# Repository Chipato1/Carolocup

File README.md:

# Carolocup
Zentrales Repository für die Carolo-Cup Software

Driving Vision Compile command: 
g++ $(pkg-config --cflags --libs /usr/local/Cellar/opencv/4.1.1_2/lib/pkgconfig/opencv4.pc) -std=c++11 /Users/beni/Desktop/Studium/Studienarbeit/OpenCV/QRCode/QRCode/main.cpp -o TestProgramm

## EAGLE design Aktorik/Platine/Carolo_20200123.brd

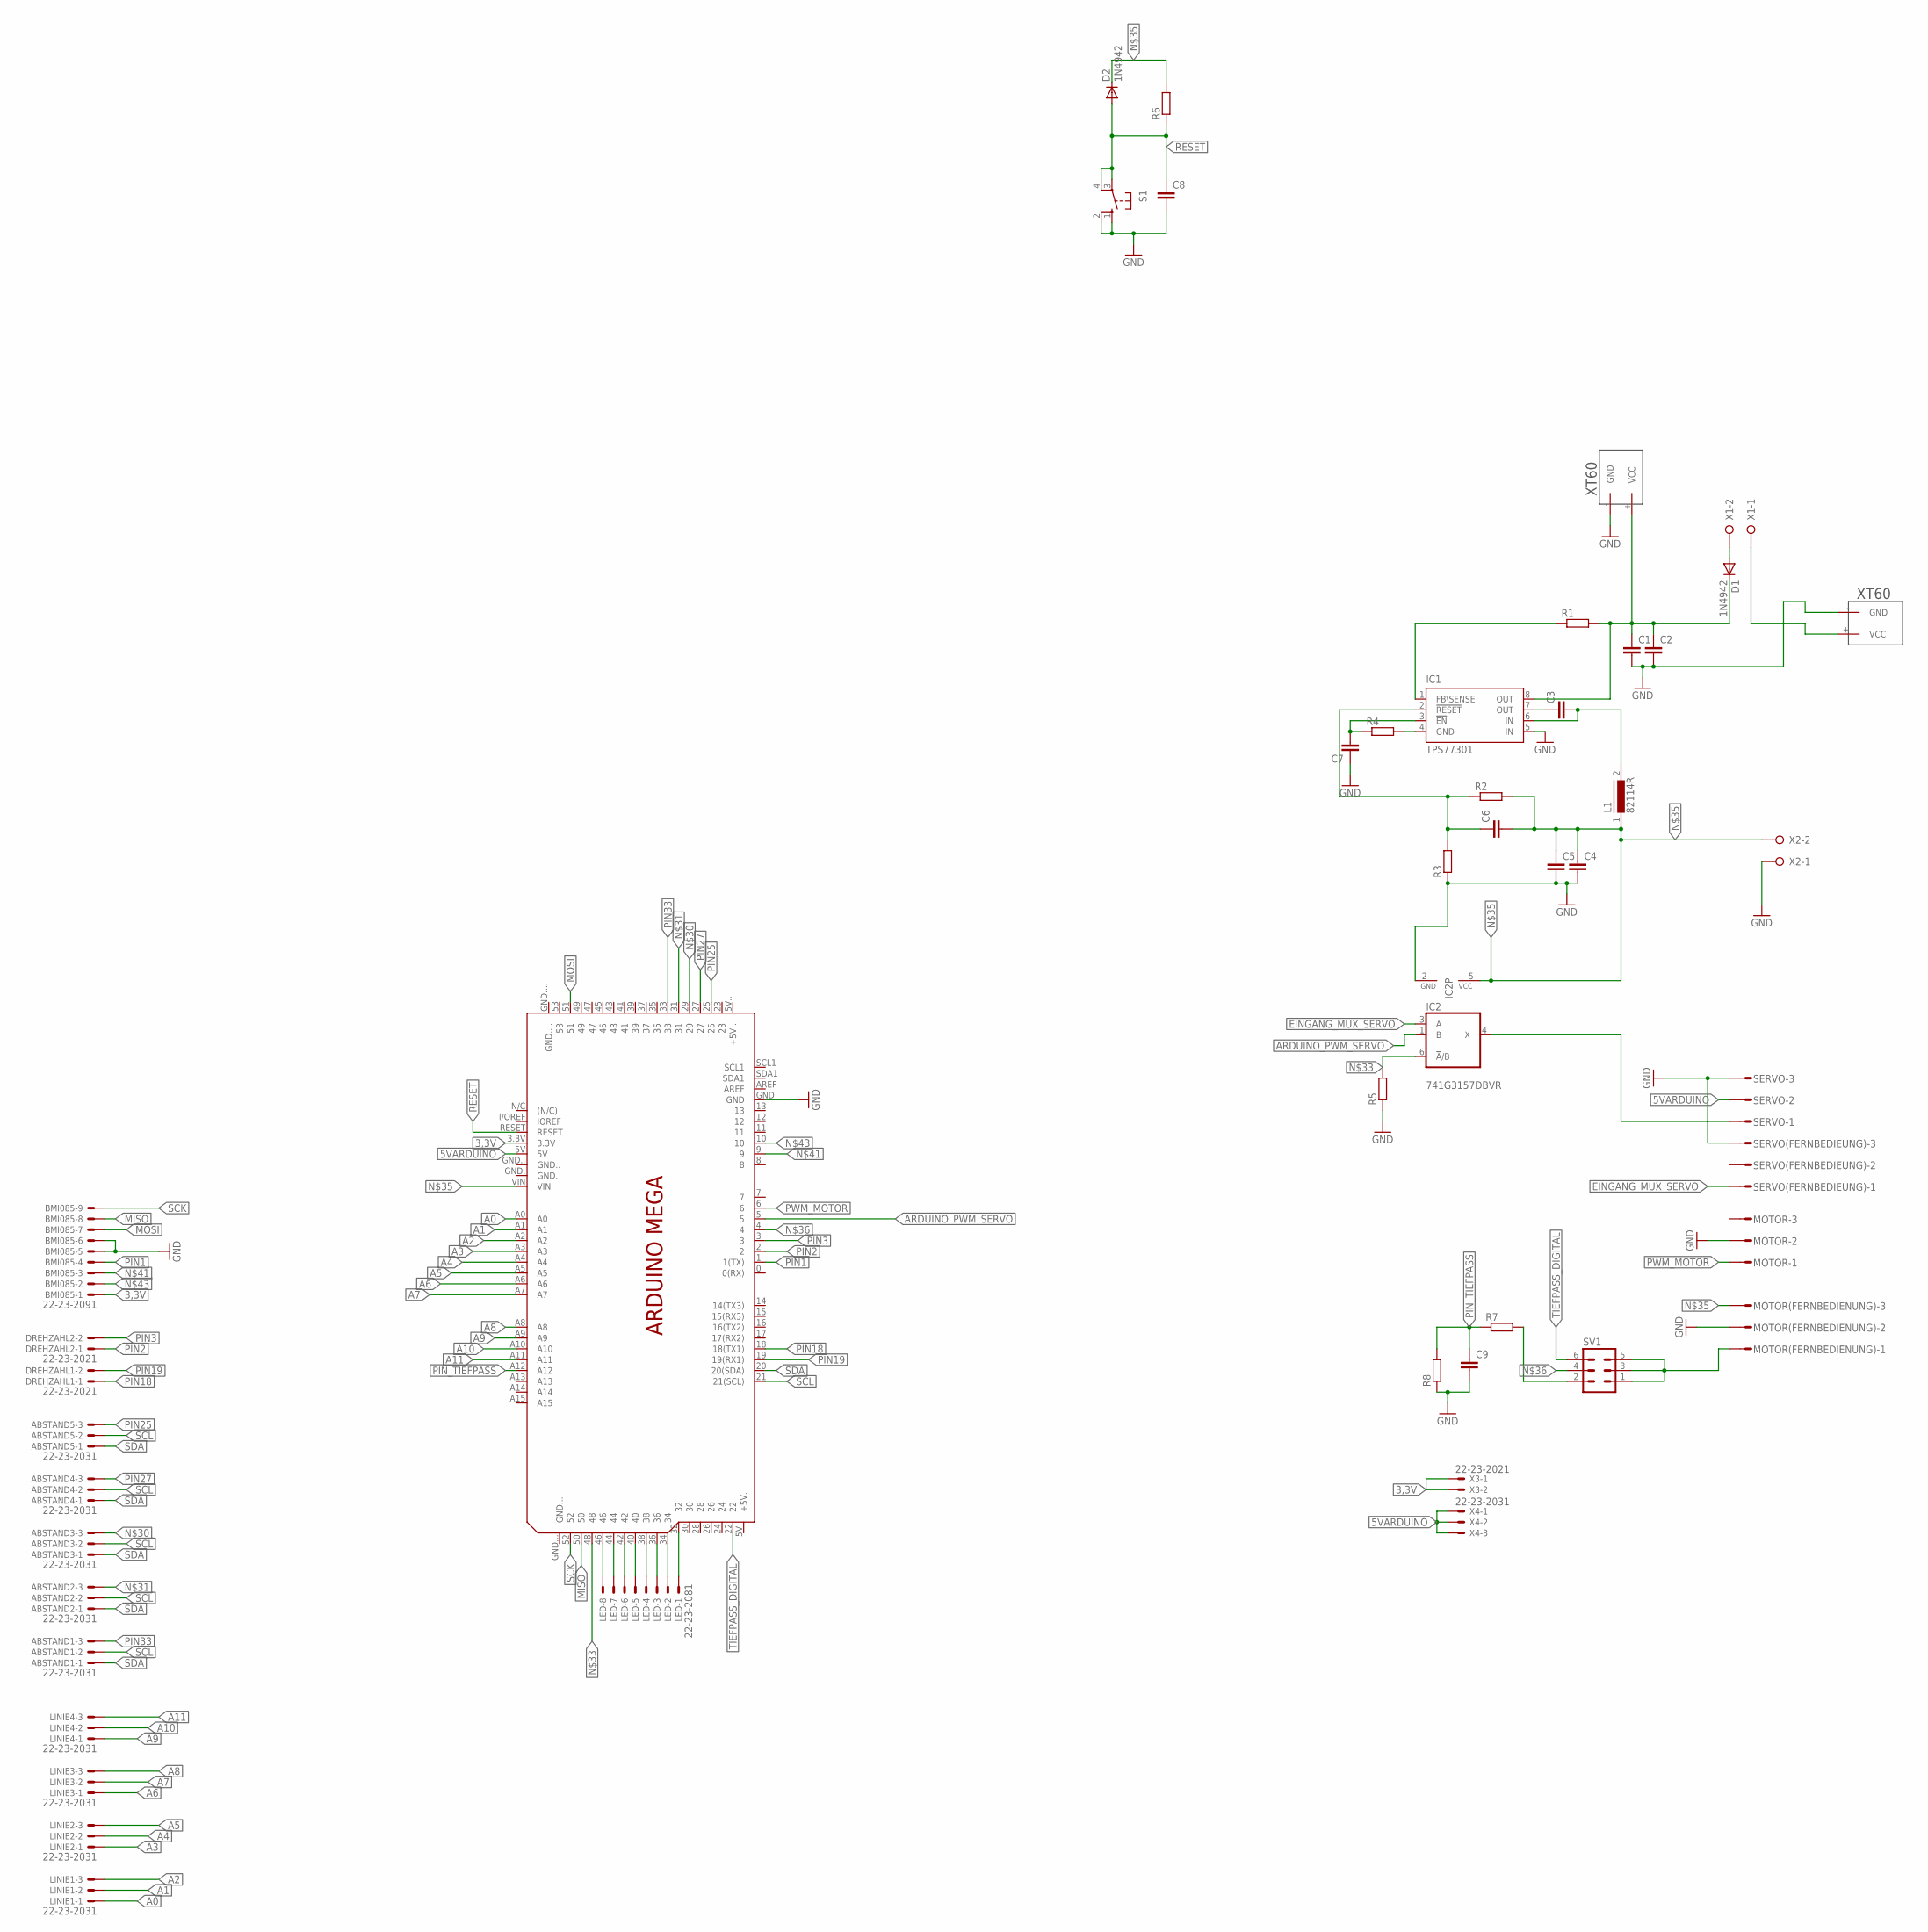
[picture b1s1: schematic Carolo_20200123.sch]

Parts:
ABSTAND1, ABSTAND2, ABSTAND3, ABSTAND4, ABSTAND5: 22-23-2031
BMI085: 22-23-2091
C1, C2, C3, C4, C5, C6, C7, C8, C9: C2,5-3; C2.5-3
D1, D2: 1N4942; DO41-10
DREHZAHL1, DREHZAHL2: 22-23-2021
IC1: TPS77301; SOP-08
IC2: 741G3157DBVR; DBV_R-PDSO-G6
L1: 82114R
LED: 22-23-2081
LINIE1, LINIE2, LINIE3, LINIE4: 22-23-2031
MOTOR: L03P
MOTOR(FERNBEDIENUNG): L03P
PCB1: ARDUINO_MEGA
R1, R2, R3, R4, R5, R6, R7, R8: R-EU_0411/15; 0411/15
S1: 10-XX; B3F-10XX
SERVO: L03P
SERVO(FERNBEDIEUNG): L03P
SV1: ML6
U$1, U$2: XT60
X1, X2: W237-02P; W237-132
X3: 22-23-2021
X4: 22-23-2031

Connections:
3,3V: BMI085.1, PCB1.3.3V, X3.1, X3.2
5VARDUINO: PCB1.5V, SERVO.2, X4.1, X4.2, X4.3
A0: LINIE1.1, PCB1.A0
A1: LINIE1.2, PCB1.A1
A2: LINIE1.3, PCB1.A2
A3: LINIE2.1, PCB1.A3
A4: LINIE2.2, PCB1.A4
A5: LINIE2.3, PCB1.A5
A6: LINIE3.1, PCB1.A6
A7: LINIE3.2, PCB1.A7
A8: LINIE3.3, PCB1.A8
A9: LINIE4.1, PCB1.A9
A10: LINIE4.2, PCB1.A10
A11: LINIE4.3, PCB1.A11
ARDUINO_PWM_SERVO: IC2.1 (B), PCB1.5
EINGANG_MUX_SERVO: IC2.3 (A), SERVO(FERNBEDIEUNG).1
GND: BMI085.5, BMI085.6, C1.2, C2.2, C4.2, C5.2, C7.1, C8.2, C9.2, IC1.5 (IN), IC2.2 (GND), MOTOR.2, MOTOR(FERNBEDIENUNG).2, PCB1.GND, R3.1, R5.1, R8.1, S1.1 (S), S1.2 (S1), SERVO.3, SERVO(FERNBEDIEUNG).3, U$1.- (GND), U$2.- (GND), X2.1
MISO: BMI085.8, PCB1.50
MOSI: BMI085.7, PCB1.51
unnamed: U$1.+ (VCC), X1.1
unnamed: R7.2, SV1.2
unnamed: C6.1, IC1.2 (!RESET), R2.1, R3.2
unnamed: C3.1, IC1.7 (OUT)
unnamed: MOTOR(FERNBEDIENUNG).1, SV1.1, SV1.3, SV1.5
unnamed: LED.1, PCB1.32
unnamed: C3.2, IC1.6 (IN), L1.2
unnamed: C7.2, IC1.3 (!EN), R4.1
unnamed: IC2.4 (X), SERVO.1
unnamed: LED.2, PCB1.34
unnamed: LED.3, PCB1.36
unnamed: LED.4, PCB1.38
unnamed: LED.5, PCB1.40
unnamed: LED.6, PCB1.42
unnamed: LED.7, PCB1.44
unnamed: LED.8, PCB1.46
unnamed: IC1.4 (GND), R4.2
unnamed: D1.A, X1.2
unnamed: C1.1, C2.1, D1.C, IC1.8 (OUT), R1.2, U$2.+ (VCC)
unnamed: ABSTAND3.3, PCB1.29
unnamed: ABSTAND2.3, PCB1.31
unnamed: IC1.1 (FB\SENSE), R1.1
unnamed: IC2.6 (!A!/B), PCB1.48, R5.2
unnamed: C4.1, C5.1, C6.2, D2.C, IC2.5 (VCC), L1.1, MOTOR(FERNBEDIENUNG).3, PCB1.VIN, R2.2, R6.2, X2.2
unnamed: PCB1.4, SV1.4
unnamed: BMI085.3, PCB1.9
unnamed: BMI085.2, PCB1.10
PIN1: BMI085.4, PCB1.1 (1(TX))
PIN2: DREHZAHL2.1, PCB1.2
PIN3: DREHZAHL2.2, PCB1.3
PIN18: DREHZAHL1.1, PCB1.18 (18(TX1))
PIN19: DREHZAHL1.2, PCB1.19 (19(RX1))
PIN25: ABSTAND5.3, PCB1.25
PIN27: ABSTAND4.3, PCB1.27
PIN33: ABSTAND1.3, PCB1.33
PIN_TIEFPASS: C9.1, PCB1.A12, R7.1, R8.2
PWM_MOTOR: MOTOR.1, PCB1.6
RESET: C8.1, D2.A, PCB1.RESET, R6.1, S1.3, S1.4 (P1)
SCK: BMI085.9, PCB1.52
SCL: ABSTAND1.2, ABSTAND2.2, ABSTAND3.2, ABSTAND4.2, ABSTAND5.2, PCB1.21 (21(SCL))
SDA: ABSTAND1.1, ABSTAND2.1, ABSTAND3.1, ABSTAND4.1, ABSTAND5.1, PCB1.20 (20(SDA))
TIEFPASS_DIGITAL: PCB1.22, SV1.6

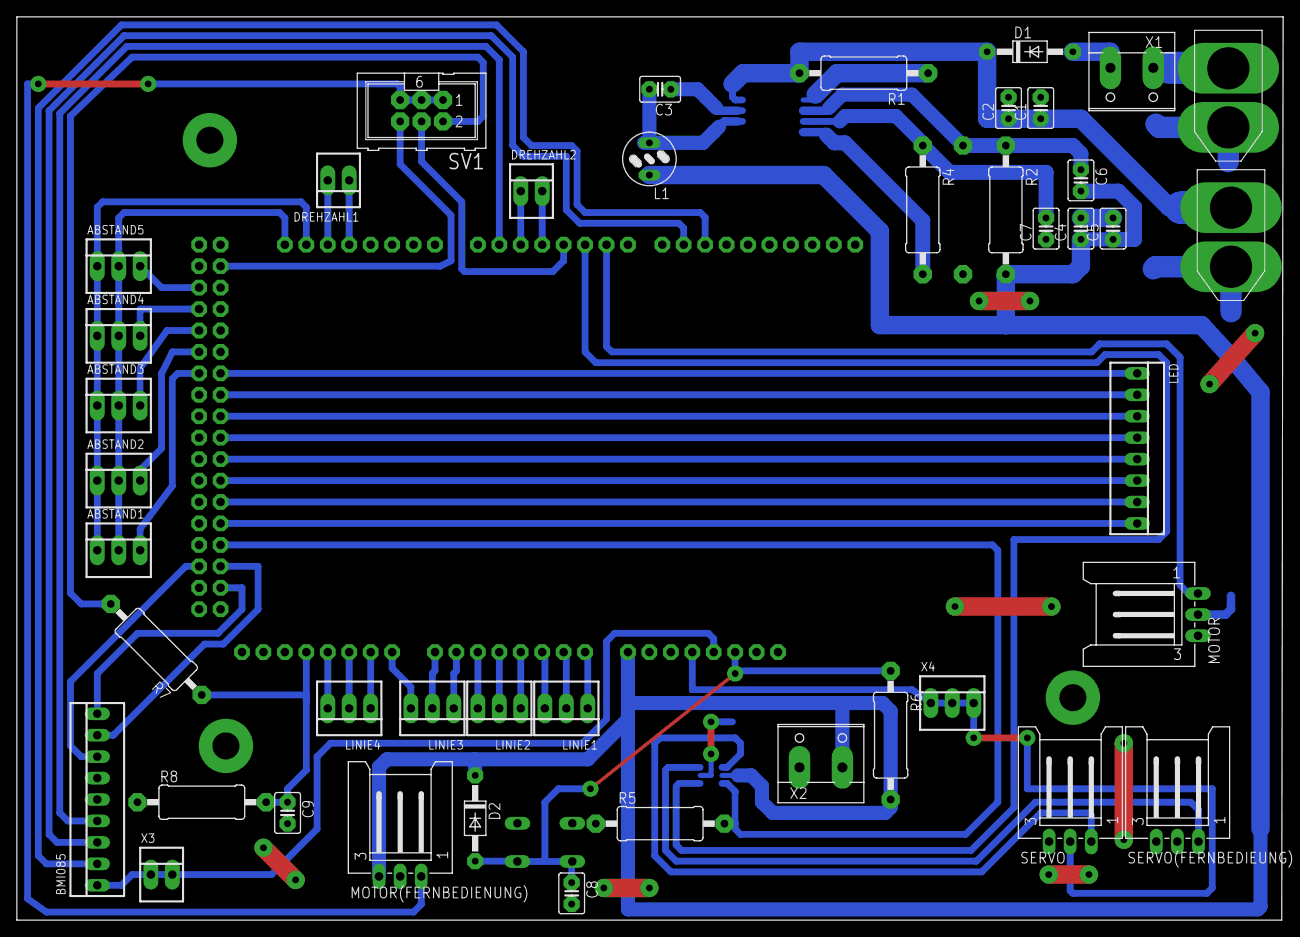
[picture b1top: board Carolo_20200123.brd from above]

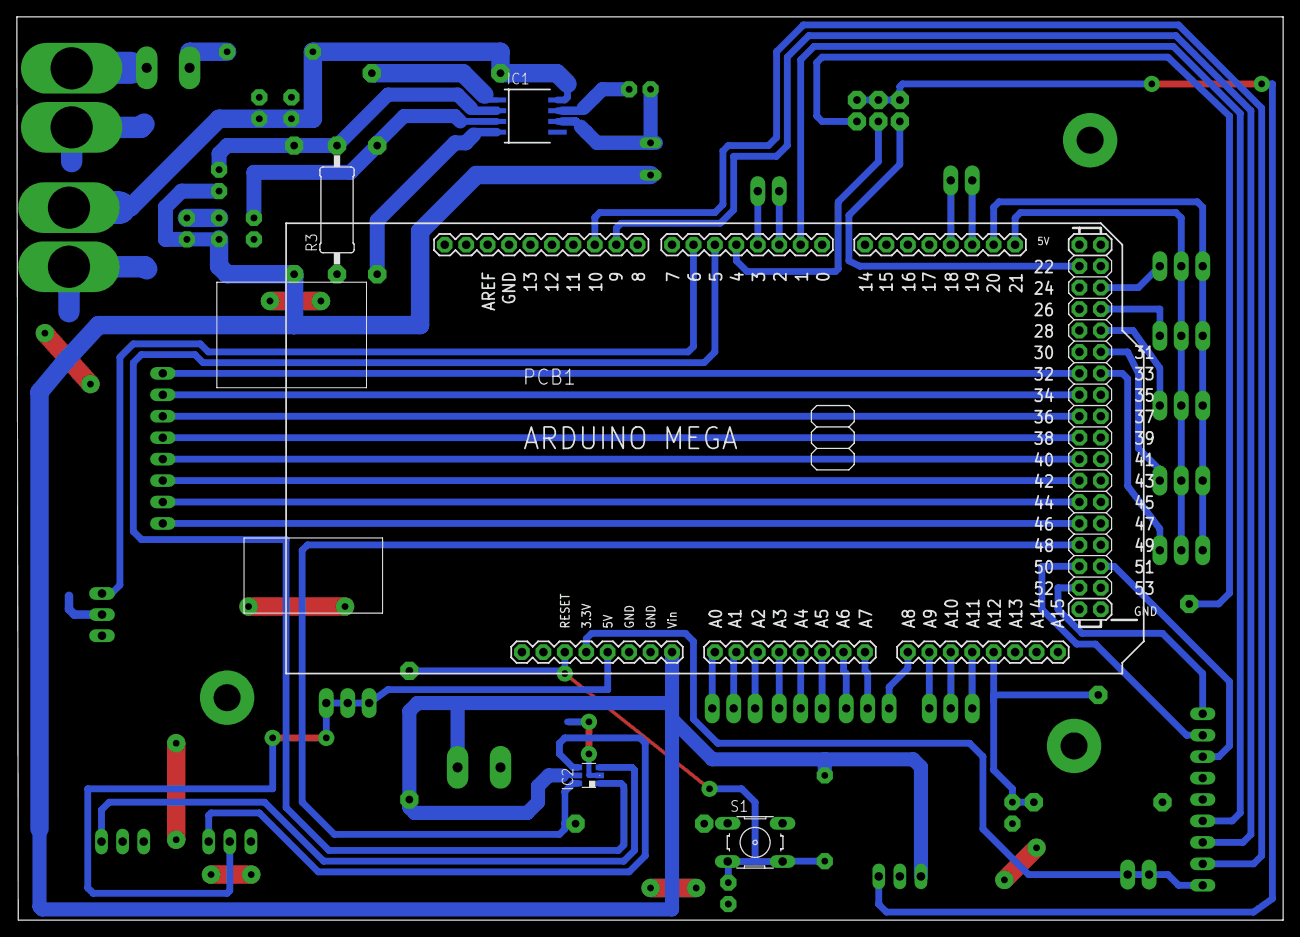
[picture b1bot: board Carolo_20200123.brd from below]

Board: 2 copper layers, 150.0 x 107.0 mm, 48 parts (5 on the bottom side), 61 nets.

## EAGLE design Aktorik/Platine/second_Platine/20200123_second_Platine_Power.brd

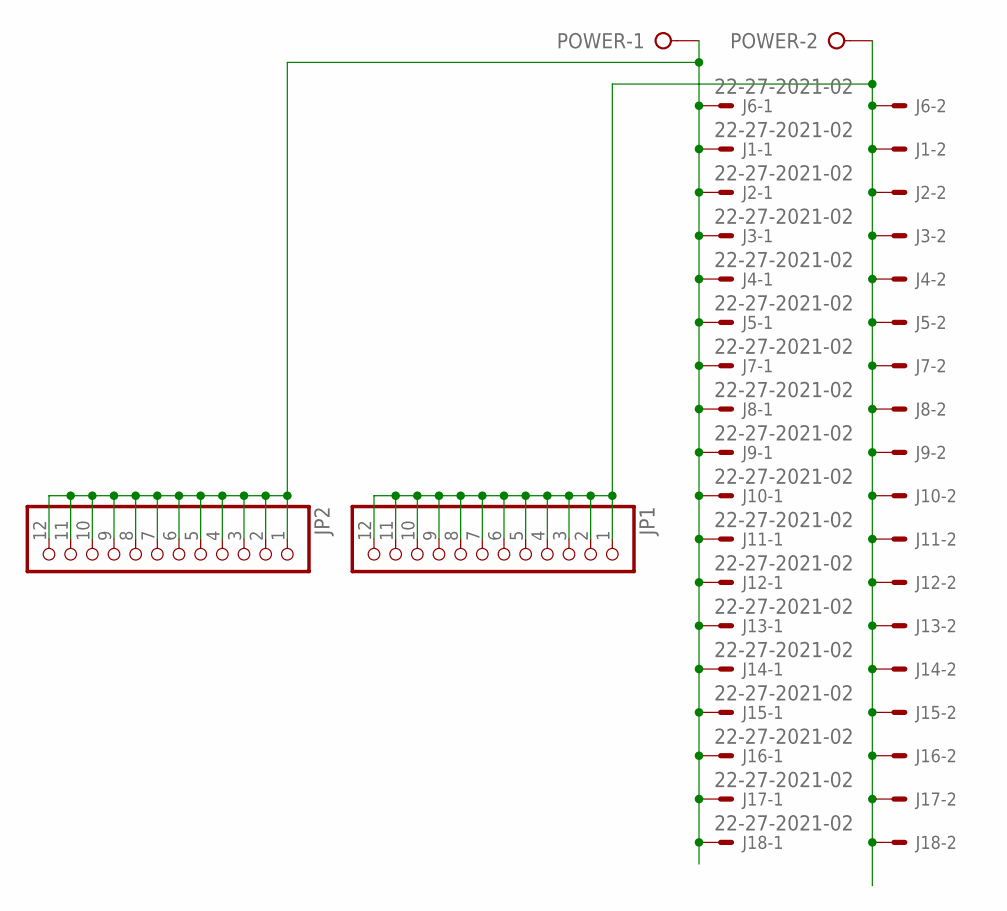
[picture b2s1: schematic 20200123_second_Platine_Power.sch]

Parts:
J1, J2, J3, J4, J5, J6, J7, J8, J9, J10, J11, J12, J13, J14, J15, J16, J17, J18: 22-27-2021-02; 6410-02
JP1, JP2: PINHD-1X12; 1X12
POWER: W237-02P; W237-132

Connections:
+5V: J1.1, J2.1, J3.1, J4.1, J5.1, J6.1, J7.1, J8.1, J9.1, J10.1, J11.1, J12.1, J13.1, J14.1, J15.1, J16.1, J17.1, J18.1, JP2.1, JP2.2, JP2.3, JP2.4, JP2.5, JP2.6, JP2.7, JP2.8, JP2.9, JP2.10, JP2.11, JP2.12, POWER.1
GND: J1.2, J2.2, J3.2, J4.2, J5.2, J6.2, J7.2, J8.2, J9.2, J10.2, J11.2, J12.2, J13.2, J14.2, J15.2, J16.2, J17.2, J18.2, JP1.1, JP1.2, JP1.3, JP1.4, JP1.5, JP1.6, JP1.7, JP1.8, JP1.9, JP1.10, JP1.11, JP1.12, POWER.2

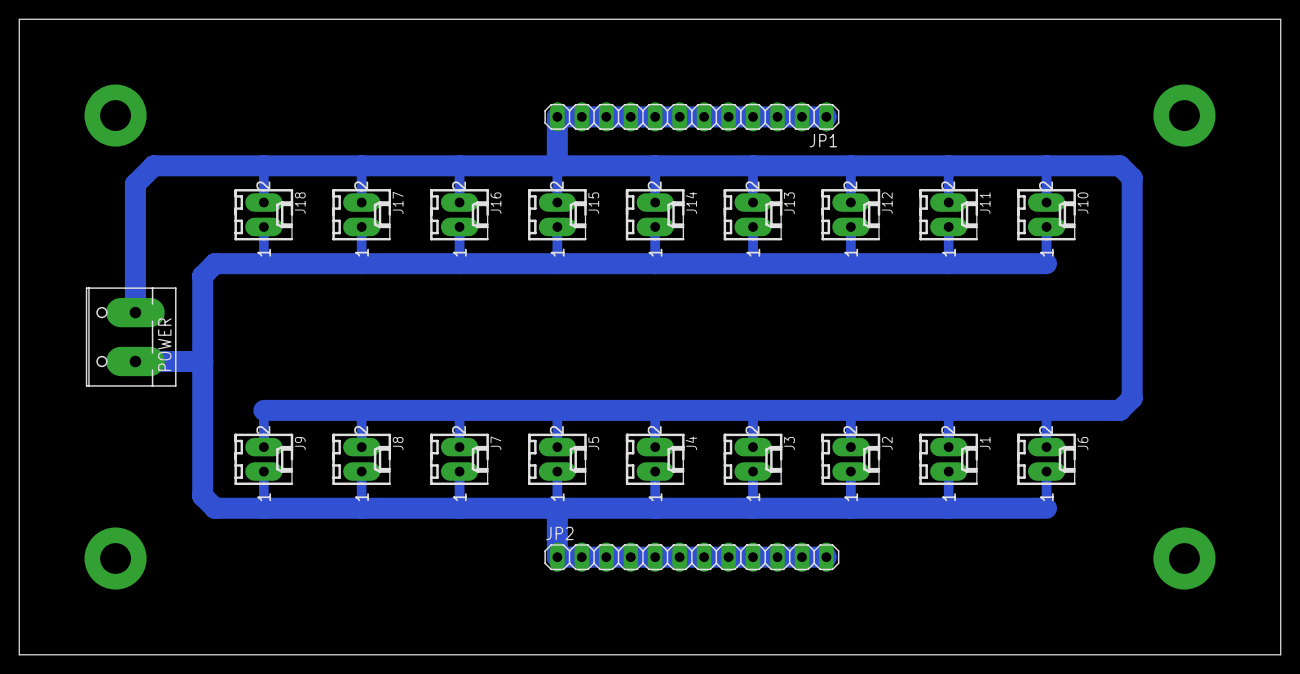
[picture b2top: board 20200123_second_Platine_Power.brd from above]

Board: 2 copper layers, 131.0 x 66.0 mm, 21 parts (0 on the bottom side), 2 nets.

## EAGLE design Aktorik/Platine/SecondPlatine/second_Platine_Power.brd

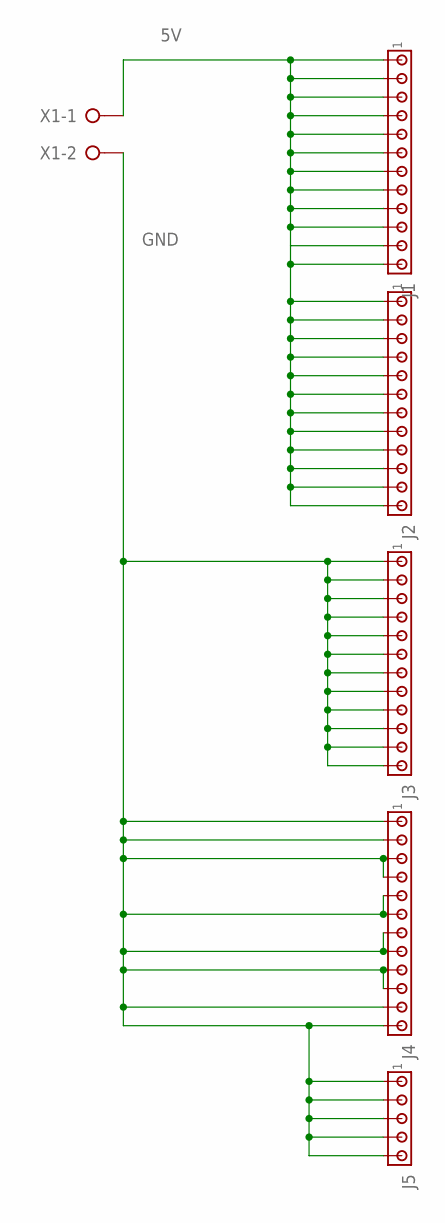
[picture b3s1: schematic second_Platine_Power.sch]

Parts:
J1, J2, J3, J4: MTA12-156; 1X12MTA
J5: MTA05-156; 1X5MTA
X1: W237-02P; W237-132

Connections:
5V: J1.1, J1.2, J1.3, J1.4, J1.5, J1.6, J1.7, J1.8, J1.9, J1.10, J1.11, J1.12, J2.1, J2.2, J2.3, J2.4, J2.5, J2.6, J2.7, J2.8, J2.9, J2.10, J2.11, J2.12, X1.1
GND: J3.1, J3.2, J3.3, J3.4, J3.5, J3.6, J3.7, J3.8, J3.9, J3.10, J3.11, J3.12, J4.1, J4.2, J4.3, J4.4, J4.5, J4.6, J4.7, J4.8, J4.9, J4.10, J4.11, J4.12, J5.1, J5.2, J5.3, J5.4, J5.5, X1.2

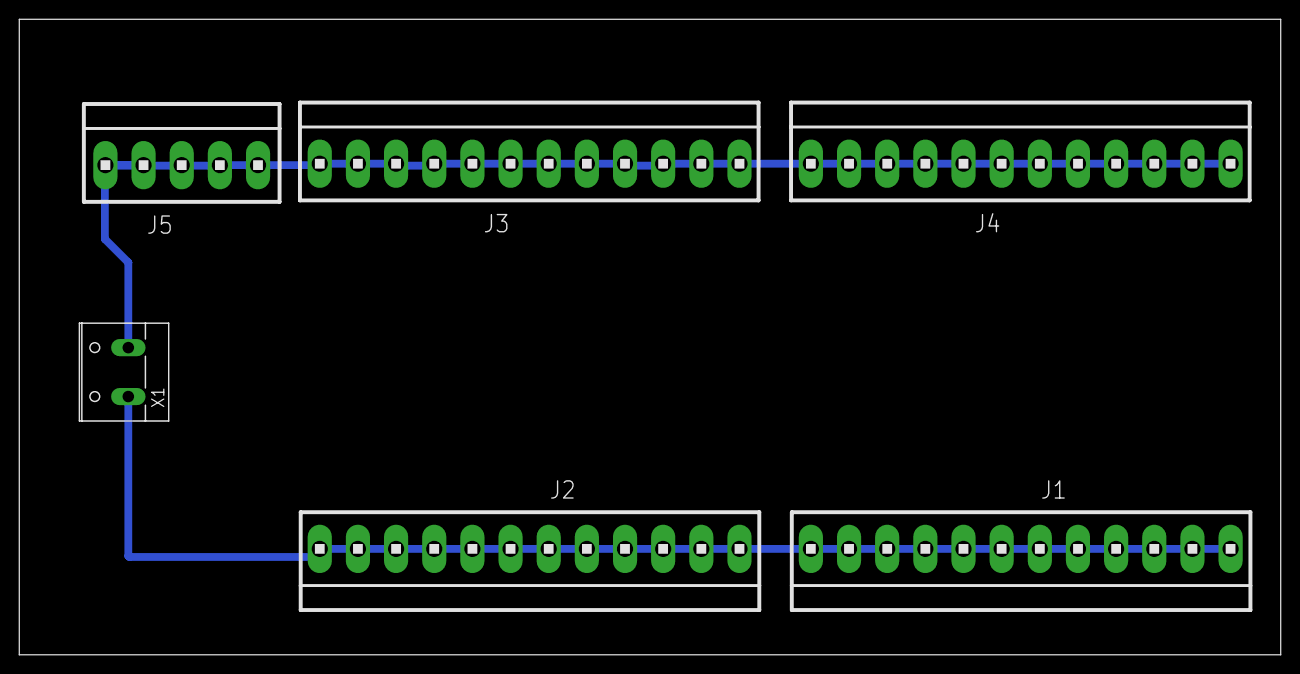
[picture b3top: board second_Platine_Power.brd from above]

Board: 2 copper layers, 131.0 x 66.0 mm, 6 parts (0 on the bottom side), 2 nets.

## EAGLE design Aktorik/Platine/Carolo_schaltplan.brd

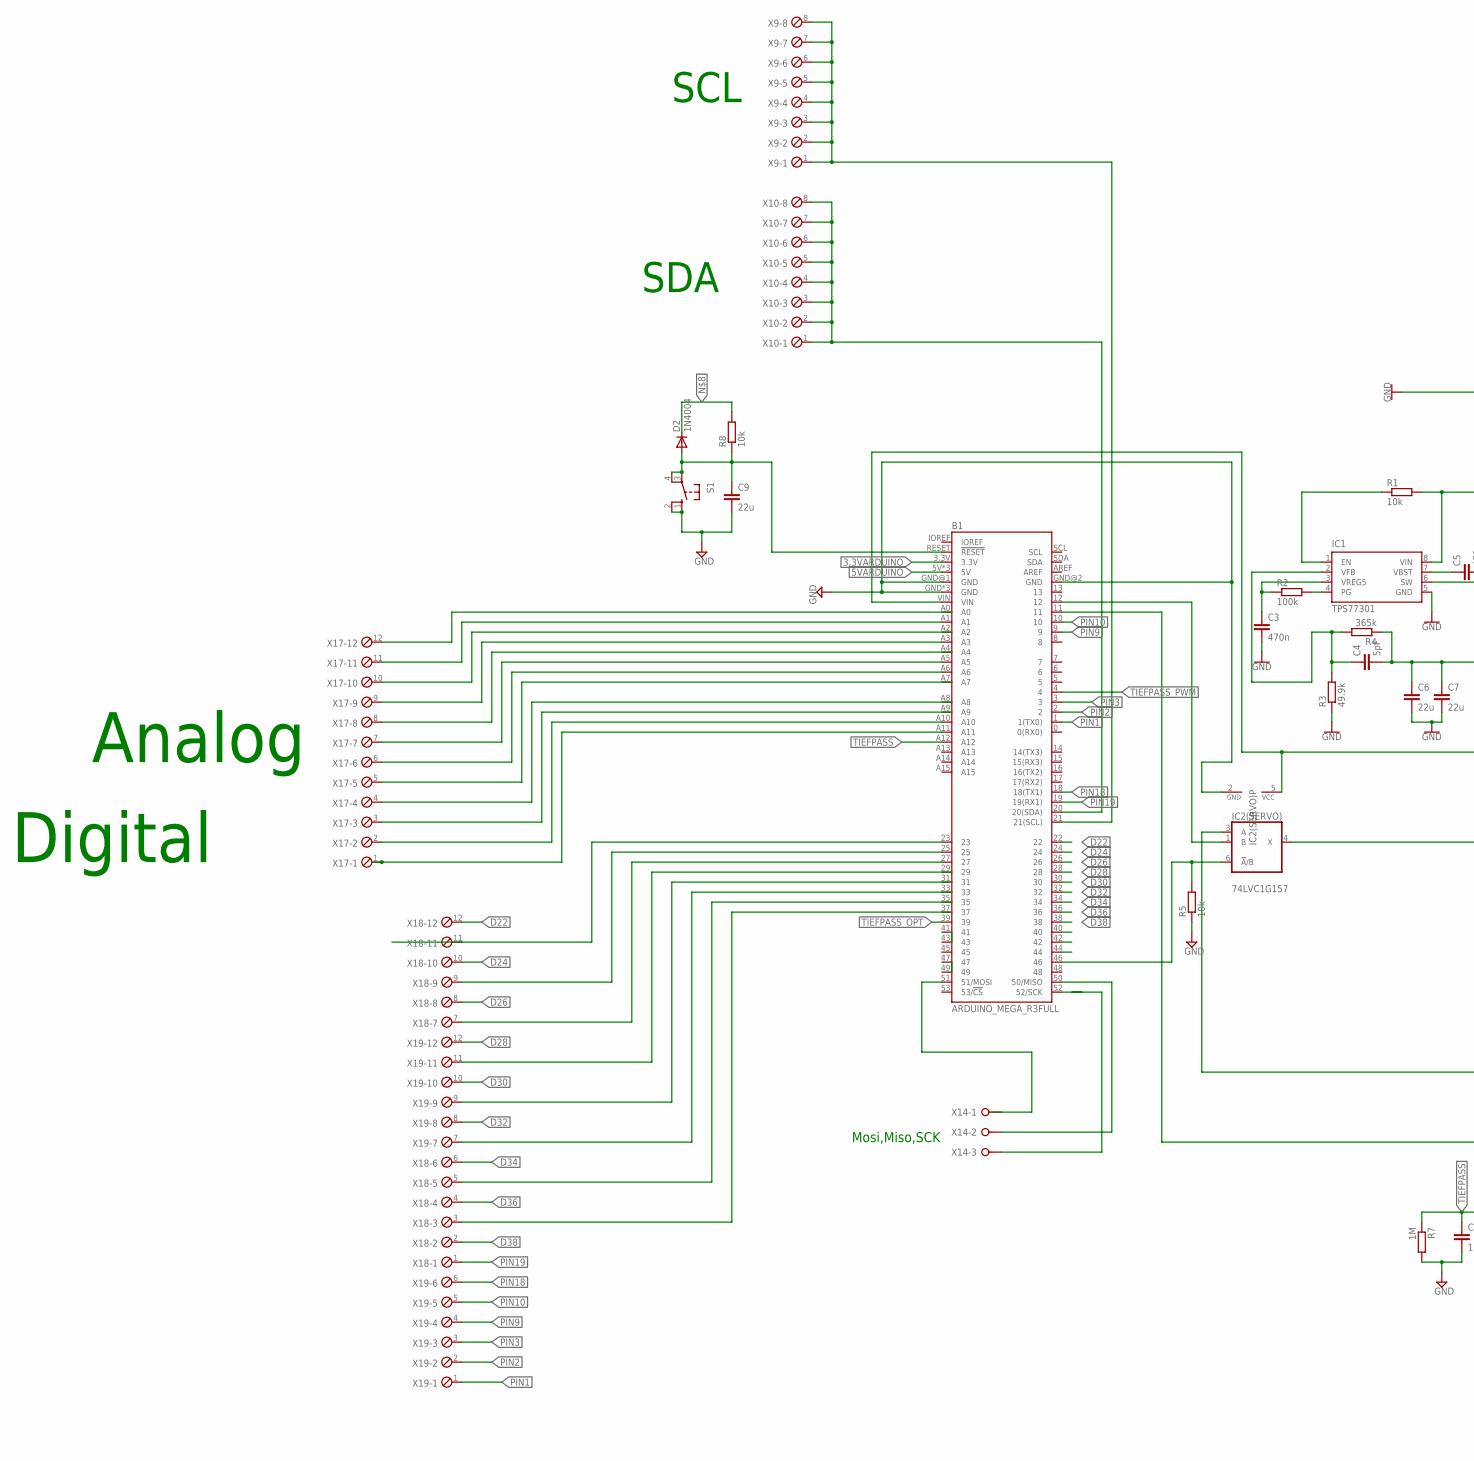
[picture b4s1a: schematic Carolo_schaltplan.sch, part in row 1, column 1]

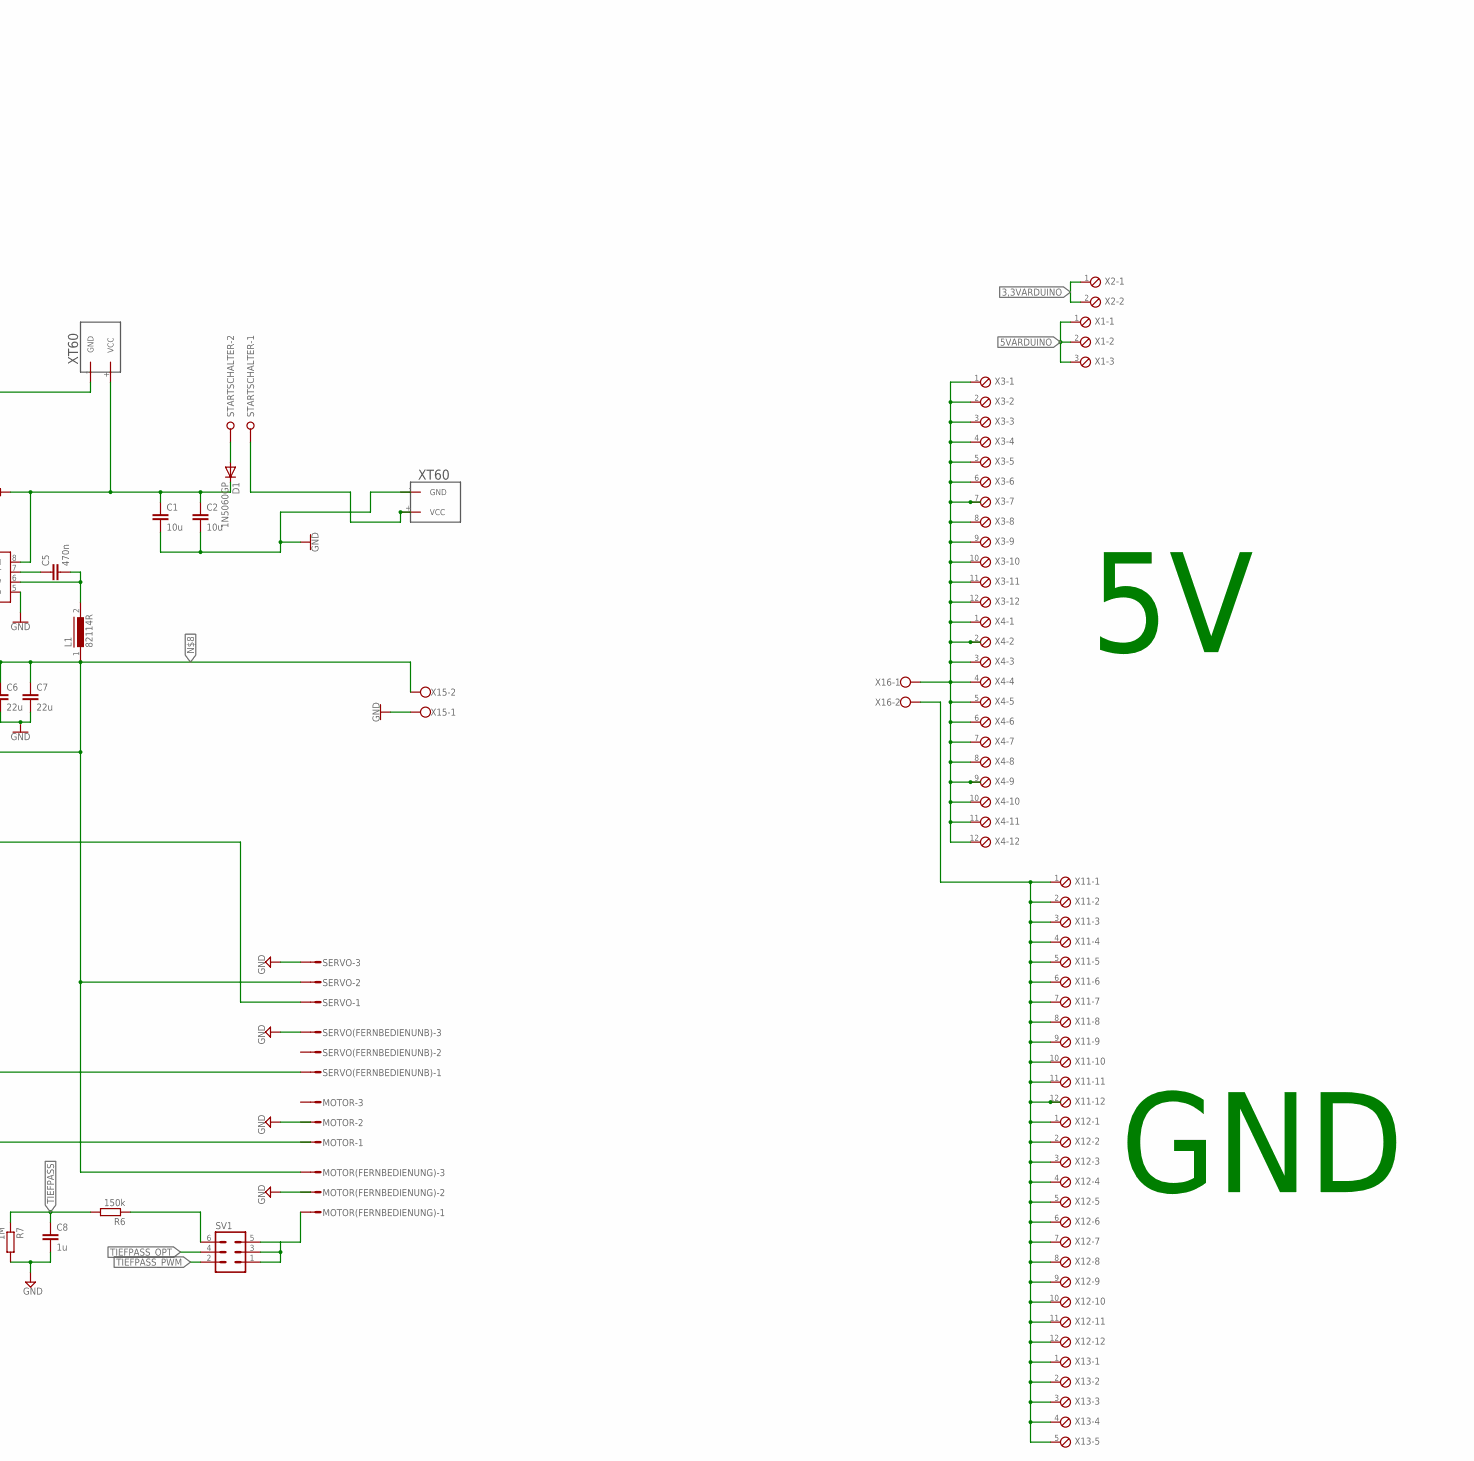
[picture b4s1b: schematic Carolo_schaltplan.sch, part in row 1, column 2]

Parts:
B1: ARDUINO_MEGA_R3FULL; ARDUINO_MEGA_NO_SILK
C1, C2: 10u; C5B2.5
C3, C5: 470n; C5B2.5
C4: 5pF; C5B2.5
C6, C7, C9: 22u; C5B2.5
C8: 1u; C5B2.5
D1: 1N5060GP; DO15-12
D2: 1N4004; DO41-10
IC1: TPS77301; SOP-08
IC2(SERVO): 74LVC1G157; DBV_R-PDSO-G6
L1: 82114R
MOTOR: L03P
MOTOR(FERNBEDIENUNG): L03P
R1, R5, R8: 10k; 0309/12
R2: 100k; 0309/12
R3: 49.9k; 0309/12
R4: 365k; 0309/12
R6: 150k; 0309/12
R7: 1M; 0309/12
S1: 10-XX; B3F-10XX
SERVO: L03P
SERVO(FERNBEDIENUNB): L03P
STARTSCHALTER: W237-02P; W237-132
SV1: ML6
U$1, U$2: XT60
X1: MPT3; 3POL254
X2: MPT2; 2POL254
X3, X4, X11, X12, X17, X18, X19: MPT12; 12POL254
X9, X10: MPT8; 8POL254
X13: MPT5; 5POL254
X14: W237-03P; W237-133
X15, X16: W237-102

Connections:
3,3VARDUINO: B1.3.3V, X2.1, X2.2
5VARDUINO: B1.5V, B1.5V@1 (5V), B1.5V@2 (5V), X1.1, X1.2, X1.3
D22: B1.22, X18.12
D24: B1.24, X18.10
D26: B1.26, X18.8
D28: B1.28, X19.12
D30: B1.30, X19.10
D32: B1.32, X19.8
D34: B1.34, X18.6
D36: B1.36, X18.4
D38: B1.38, X18.2
D40: B1.40
D42: B1.42
D44: B1.44
GND: B1.GND, B1.GND@1 (GND), B1.GND@2 (GND), B1.GND@3 (GND), B1.GND@4 (GND), C1.2, C2.2, C3.2, C6.2, C7.2, C8.2, C9.2, IC1.5 (GND), IC2(SERVO).2 (GND), R3.1, R5.1, R7.2, S1.1 (S), S1.2 (S1), SERVO.3, SERVO(FERNBEDIENUNB).3, U$2.- (GND), X15.1
unnamed: B1.RESET (!RESET), C9.1, D2.A, R8.1, S1.3, S1.4 (P1)
unnamed: C1.1, C2.1, D1.C, IC1.8 (VIN), R1.2, U$2.+ (VCC)
unnamed: C4.1, IC1.2 (VFB), R3.2, R4.2
unnamed: IC1.4 (PG), R2.2
unnamed: X11.1, X11.2, X11.3, X11.4, X11.5, X11.6, X11.7, X11.8, X11.9, X11.10, X11.11, X11.12, X12.1, X12.2, X12.3, X12.4, X12.5, X12.6, X12.7, X12.8, X12.9, X12.10, X12.11, X12.12, X13.1, X13.2, X13.3, X13.4, X13.5, X16.2
unnamed: C5.1, IC1.7 (VBST)
unnamed: B1.VIN, C4.2, C6.1, C7.1, D2.C, IC2(SERVO).5 (VCC), L1.1, MOTOR(FERNBEDIENUNG).3, R4.1, R8.2, SERVO.2, X3.1, X3.2, X3.3, X3.4, X3.5, X3.6, X3.7, X3.8, X3.9, X3.10, X3.11, X3.12, X4.1, X4.2, X4.3, X4.4, X4.5, X4.6, X4.7, X4.8, X4.9, X4.10, X4.11, X4.12, X15.2, X16.1
unnamed: STARTSCHALTER.1, U$1.+ (VCC)
unnamed: B1.20 (20(SDA)), X10.1, X10.2, X10.3, X10.4, X10.5, X10.6, X10.7, X10.8
unnamed: IC2(SERVO).4 (X), SERVO.1
unnamed: B1.12, IC2(SERVO).1 (B)
unnamed: D1.A, STARTSCHALTER.2
unnamed: IC2(SERVO).3 (A), SERVO(FERNBEDIENUNB).1
unnamed: B1.A3, X17.9
unnamed: B1.A5, X17.7
unnamed: B1.A6, X17.6
unnamed: B1.A10, X17.2
unnamed: B1.A11, X17.1
unnamed: B1.23, X18.11
unnamed: B1.21 (21(SCL)), X9.1, X9.2, X9.3, X9.4, X9.5, X9.6, X9.7, X9.8
unnamed: B1.25, X18.9
unnamed: B1.27, X18.7
unnamed: R6.1, SV1.6
unnamed: MOTOR(FERNBEDIENUNG).1, SV1.1, SV1.3, SV1.5
unnamed: IC1.1 (EN), R1.1
unnamed: B1.52 (52/SCK), X14.3
unnamed: B1.50 (50/MISO), X14.2
unnamed: C5.2, IC1.6 (SW), L1.2
unnamed: C3.1, IC1.3 (VREG5), R2.1
unnamed: B1.A1, X17.11
PIN1: B1.1 (1(TX0)), X19.1
PIN2: B1.2, X19.2
PIN3: B1.3, X19.3
PIN9: B1.9, X19.4
PIN10: B1.10, X19.5
PIN18: B1.18 (18(TX1)), X19.6
PIN19: B1.19 (19(RX1)), X18.1
SL: B1.46, IC2(SERVO).6 (!A!/B), R5.2
TIEFPASS: B1.A12, C8.1, R6.2, R7.1
TIEFPASS_OPT: B1.39, SV1.4
TIEFPASS_PWM: B1.4, SV1.2

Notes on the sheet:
GND
Analog
Digital
SDA
SCL
Mosi,Miso,SCK

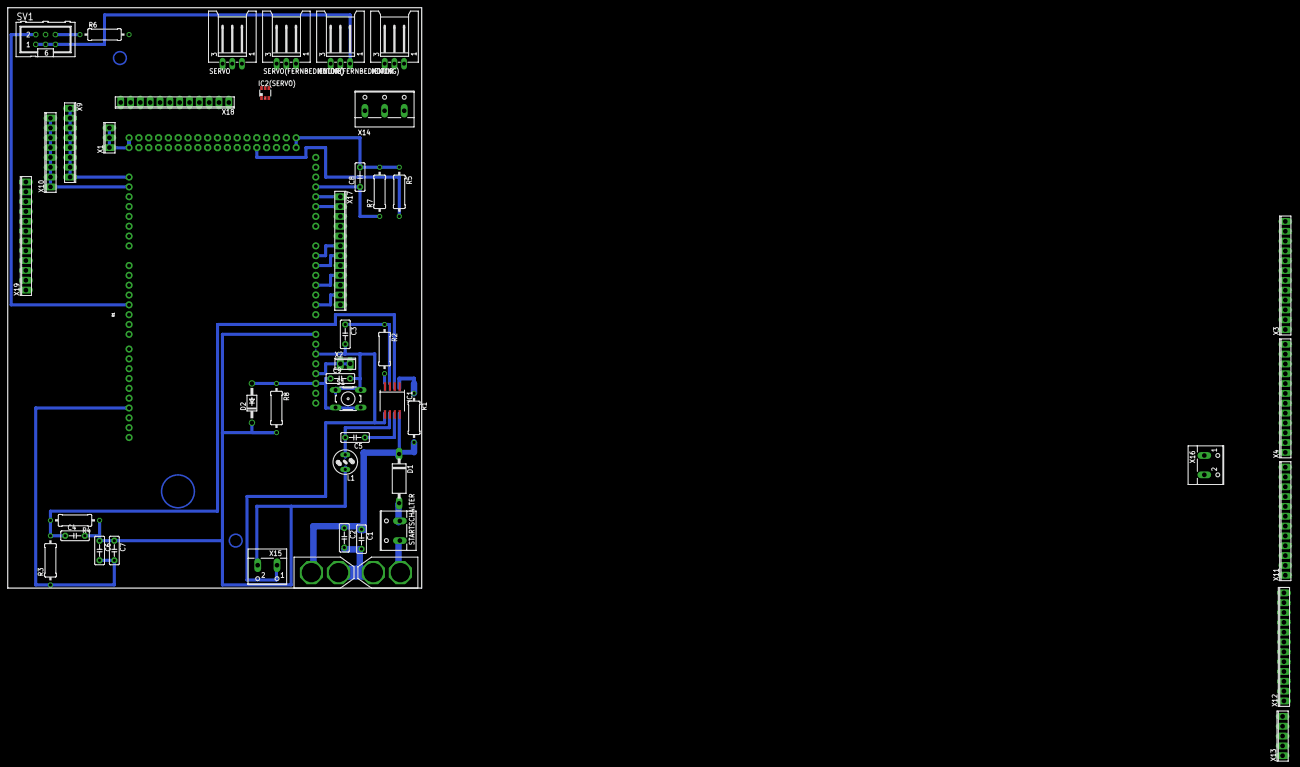
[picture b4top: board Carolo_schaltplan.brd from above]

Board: 2 copper layers, 107.0 x 150.0 mm, 47 parts (0 on the bottom side), 53 nets.

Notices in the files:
parts and their libraries:
SparkFun-Boards: Licensing: Creative Commons ShareAlike 4.0 International - https://creativecommons.org/licenses/by-sa/4.0
